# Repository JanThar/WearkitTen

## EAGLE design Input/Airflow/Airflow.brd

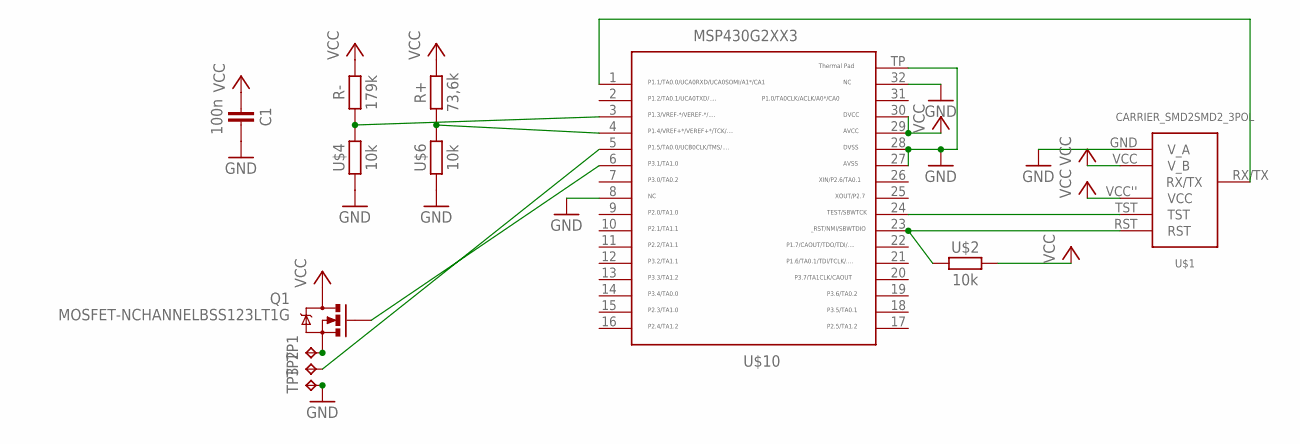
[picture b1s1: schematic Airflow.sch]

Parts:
C1: 100n; 603
Q1: MOSFET-NCHANNELBSS123LT1G; SOT23-3
R+: 73,6k; 603
R-: 179k; 603
TP1, TP2, TP3: TPTP18SQ; TP18SQ
U$1: CARRIER_SMD2SMD2_3POL; CARRIER_SMD2_3POL
U$2, U$4, U$6: 10k; 603
U$10: MSP430G2553; QFN32

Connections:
GND: C1.2, TP3.TP, U$1.GND (V_A), U$4.1, U$6.1, U$10.8, U$10.27, U$10.28, U$10.32, U$10.TP
unnamed: R-.1, U$4.2, U$10.3
unnamed: U$1.TST, U$10.24
unnamed: U$1.RST, U$2.1, U$10.23
unnamed: R+.1, U$6.2, U$10.4
unnamed: TP2.TP, U$10.5
unnamed: Q1.2 (S), TP1.TP
unnamed: Q1.1 (G), U$10.6
unnamed: U$1.RX/TX, U$10.1
VCC: C1.1, Q1.3 (D), R+.2, R-.2, U$1.VCC (V_B), U$1.VCC'' (VCC), U$2.2, U$10.29, U$10.30

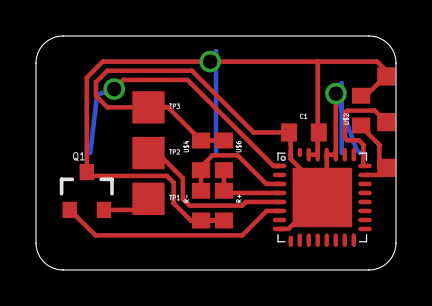
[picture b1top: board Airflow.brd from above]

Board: 2 copper layers, 20.0 x 13.0 mm, 12 parts (0 on the bottom side), 10 nets.

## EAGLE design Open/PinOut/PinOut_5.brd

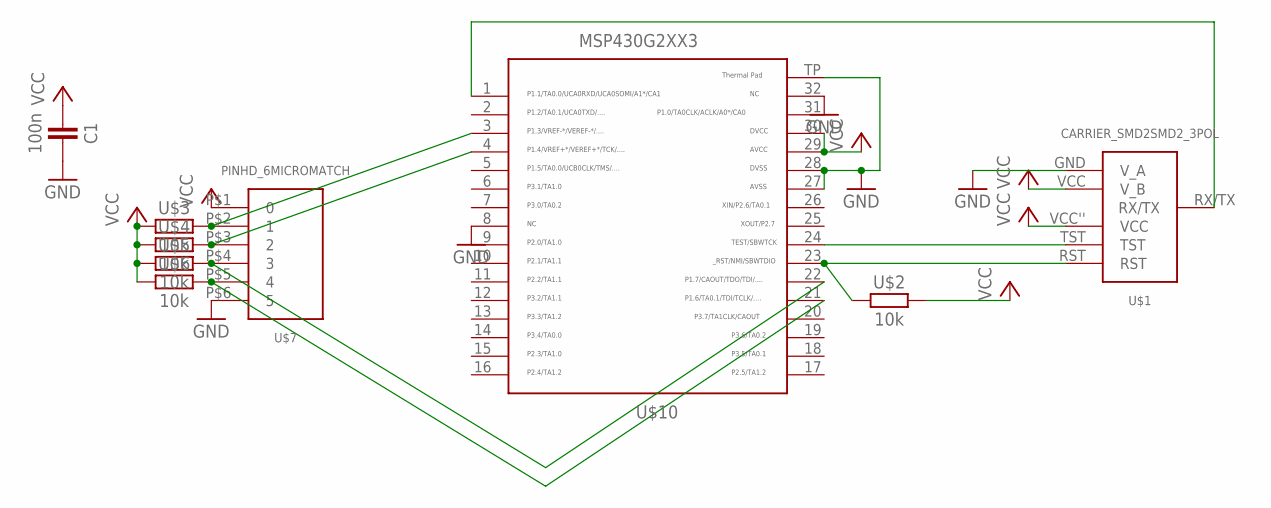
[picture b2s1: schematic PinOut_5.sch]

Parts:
C1: 100n; 603
U$1: CARRIER_SMD2SMD2_3POL; CARRIER_SMD2_3POL
U$2, U$3, U$4, U$5, U$6: 10k; 603
U$7: PINHD_6MICROMATCH; MICROMATCH6POL
U$10: MSP430G2553; QFN32

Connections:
GND: C1.2, U$1.GND (V_A), U$7.P$6 (5), U$10.8, U$10.27, U$10.28, U$10.32, U$10.TP
unnamed: U$5.2, U$7.P$4 (3), U$10.22
unnamed: U$1.TST, U$10.24
unnamed: U$1.RST, U$2.1, U$10.23
unnamed: U$6.2, U$7.P$5 (4), U$10.21
unnamed: U$4.2, U$7.P$3 (2), U$10.4
unnamed: U$3.2, U$7.P$2 (1), U$10.3
unnamed: U$1.RX/TX, U$10.1
VCC: C1.1, U$1.VCC (V_B), U$1.VCC'' (VCC), U$2.2, U$3.1, U$4.1, U$5.1, U$6.1, U$7.P$1 (0), U$10.29, U$10.30

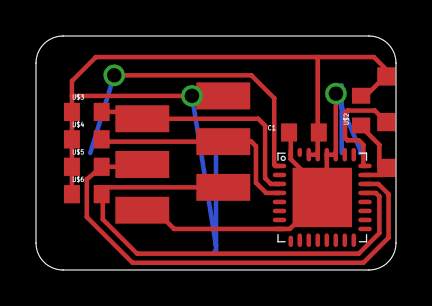
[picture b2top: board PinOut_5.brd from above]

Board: 2 copper layers, 20.0 x 13.0 mm, 9 parts (0 on the bottom side), 9 nets.

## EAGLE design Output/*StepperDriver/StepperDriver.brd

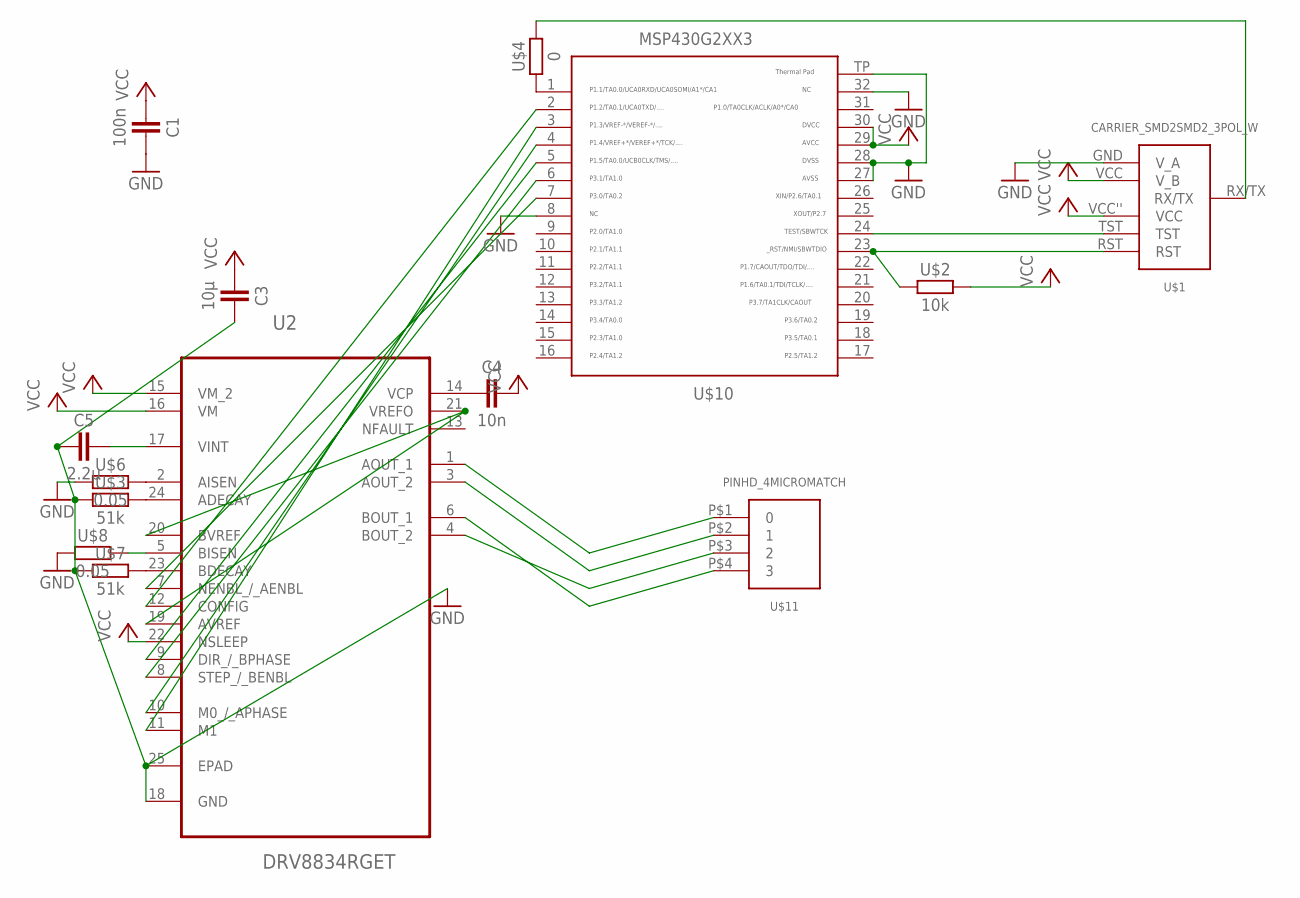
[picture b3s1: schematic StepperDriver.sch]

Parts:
C1: 100n; 603
C3: 10µ; 603
C4: 10n; 603
C5: 2.2µ; 603
U2: DRV8834RGET; QFN50P400X400X100-25N
U$1: CARRIER_SMD2SMD2_3POL_W; CARRIER_SMD2_WIDE_3POL
U$2: 10k; 603
U$3, U$7: 51k; 603
U$4: 0; 603
U$6, U$8: 0.05; 603
U$10: MSP430G2553; QFN32
U$11: PINHD_4MICROMATCH; MICROMATCH4P0L

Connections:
GND: C1.2, C3.2, C5.1, U2.18 (GND), U2.25 (EPAD), U$1.GND (V_A), U$3.1, U$6.1, U$7.1, U$8.1, U$10.8, U$10.27, U$10.28, U$10.32, U$10.TP
unnamed: C5.2, U2.17 (VINT)
unnamed: U$1.TST, U$10.24
unnamed: U$1.RST, U$2.1, U$10.23
unnamed: C4.1, U2.14 (VCP)
unnamed: U2.24 (ADECAY), U$3.2
unnamed: U2.23 (BDECAY), U$7.2
unnamed: U$4.1, U$10.1
unnamed: U$1.RX/TX, U$4.2
unnamed: U2.2 (AISEN), U$6.2
unnamed: U2.5 (BISEN), U$8.2
unnamed: U2.6 (BOUT_1), U$11.P$4 (3)
unnamed: U2.4 (BOUT_2), U$11.P$3 (2)
unnamed: U2.1 (AOUT_1), U$11.P$1 (0)
unnamed: U2.3 (AOUT_2), U$11.P$2 (1)
unnamed: U2.19 (AVREF), U2.20 (BVREF), U2.21 (VREFO)
unnamed: U2.10 (M0_/_APHASE), U$10.4
unnamed: U2.11 (M1), U$10.3
unnamed: U2.7 (NENBL_/_AENBL), U$10.7
unnamed: U2.8 (STEP_/_BENBL), U$10.6
unnamed: U2.12 (CONFIG), U$10.2
unnamed: U2.9 (DIR_/_BPHASE), U$10.5
VCC: C1.1, C3.1, C4.2, U2.15 (VM_2), U2.16 (VM), U2.22 (NSLEEP), U$1.VCC (V_B), U$1.VCC'' (VCC), U$2.2, U$10.29, U$10.30

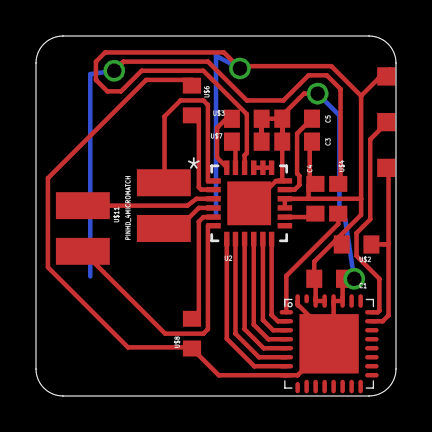
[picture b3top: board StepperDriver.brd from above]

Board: 2 copper layers, 20.0 x 20.0 mm, 14 parts (0 on the bottom side), 23 nets.

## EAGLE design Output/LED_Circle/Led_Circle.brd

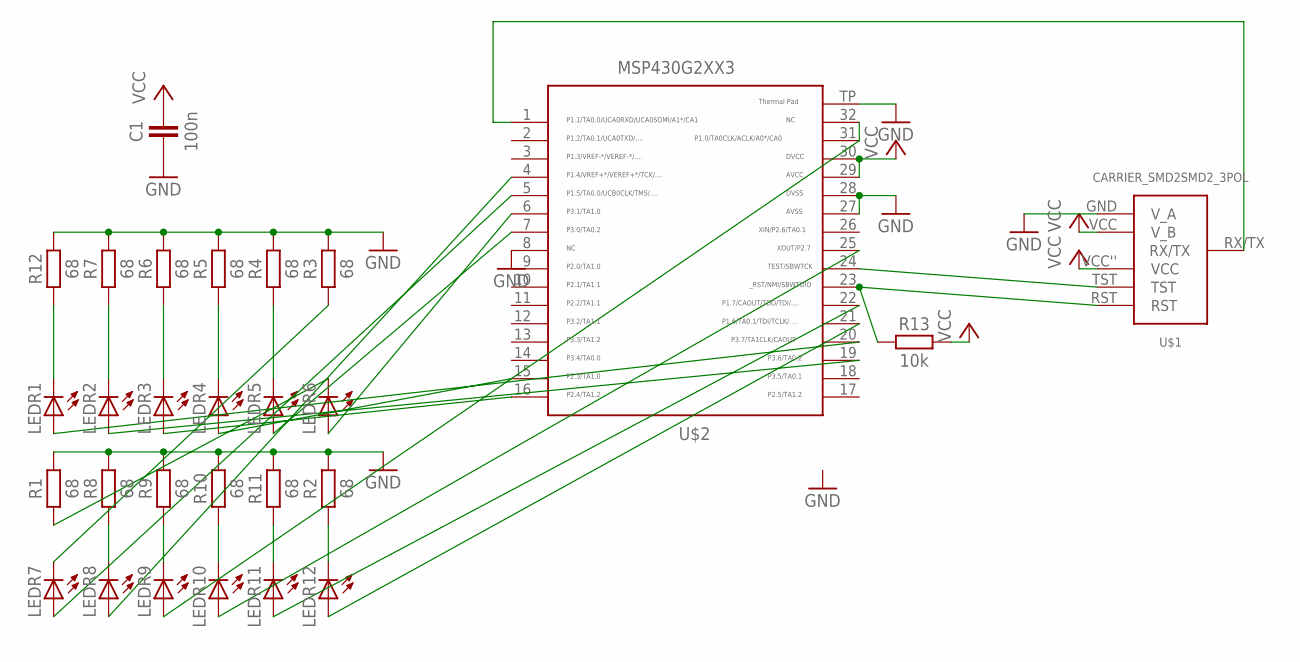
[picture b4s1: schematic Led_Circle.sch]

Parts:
C1: 100n; 603
LEDR1, LEDR2, LEDR3, LEDR4, LEDR5, LEDR6, LEDR7, LEDR8, LEDR9, LEDR10, LEDR11, LEDR12: LEDCHIPLED_0603; CHIPLED_0603
R1, R2, R3, R4, R5, R6, R7, R8, R9, R10, R11, R12: 68; 603
R13: 10k; 603
U$1: CARRIER_SMD2SMD2_3POL; CARRIER_SMD2_3POL
U$2: MSP430G2553; QFN32

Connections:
GND: C1.1, R1.2, R2.2, R3.2, R4.2, R5.2, R6.2, R7.2, R8.2, R9.2, R10.2, R11.2, R12.2, U$1.GND (V_A), U$2.8, U$2.27, U$2.28, U$2.TP
unnamed: LEDR8.A, U$2.4
unnamed: LEDR7.C, R3.1
unnamed: U$1.RX/TX, U$2.1
unnamed: LEDR12.C, R2.1
unnamed: LEDR11.C, R11.1
unnamed: LEDR10.C, R10.1
unnamed: LEDR9.C, R9.1
unnamed: LEDR8.C, R8.1
unnamed: LEDR6.C, R1.1
unnamed: LEDR5.C, R4.1
unnamed: LEDR4.C, R5.1
unnamed: LEDR3.C, R6.1
unnamed: LEDR2.C, R7.1
unnamed: LEDR1.C, R12.1
unnamed: LEDR9.A, U$2.31, U$2.32
unnamed: LEDR10.A, U$2.25
unnamed: LEDR11.A, U$2.22
unnamed: LEDR12.A, U$2.21
unnamed: LEDR1.A, U$2.20
unnamed: LEDR2.A, U$2.19
unnamed: LEDR3.A, U$2.16
unnamed: LEDR4.A, U$2.15
unnamed: LEDR5.A, U$2.7
unnamed: LEDR6.A, U$2.6
unnamed: LEDR7.A, U$2.5
RST: R13.1, U$1.RST, U$2.23
TST: U$1.TST, U$2.24
VCC: C1.2, R13.2, U$1.VCC (V_B), U$1.VCC'' (VCC), U$2.29, U$2.30

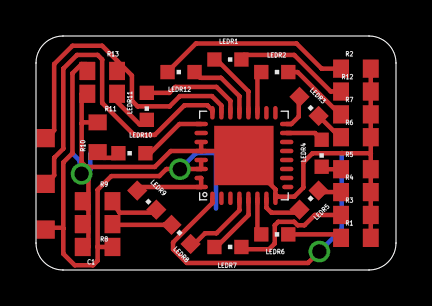
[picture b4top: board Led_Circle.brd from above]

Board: 2 copper layers, 20.0 x 13.0 mm, 28 parts (0 on the bottom side), 29 nets.

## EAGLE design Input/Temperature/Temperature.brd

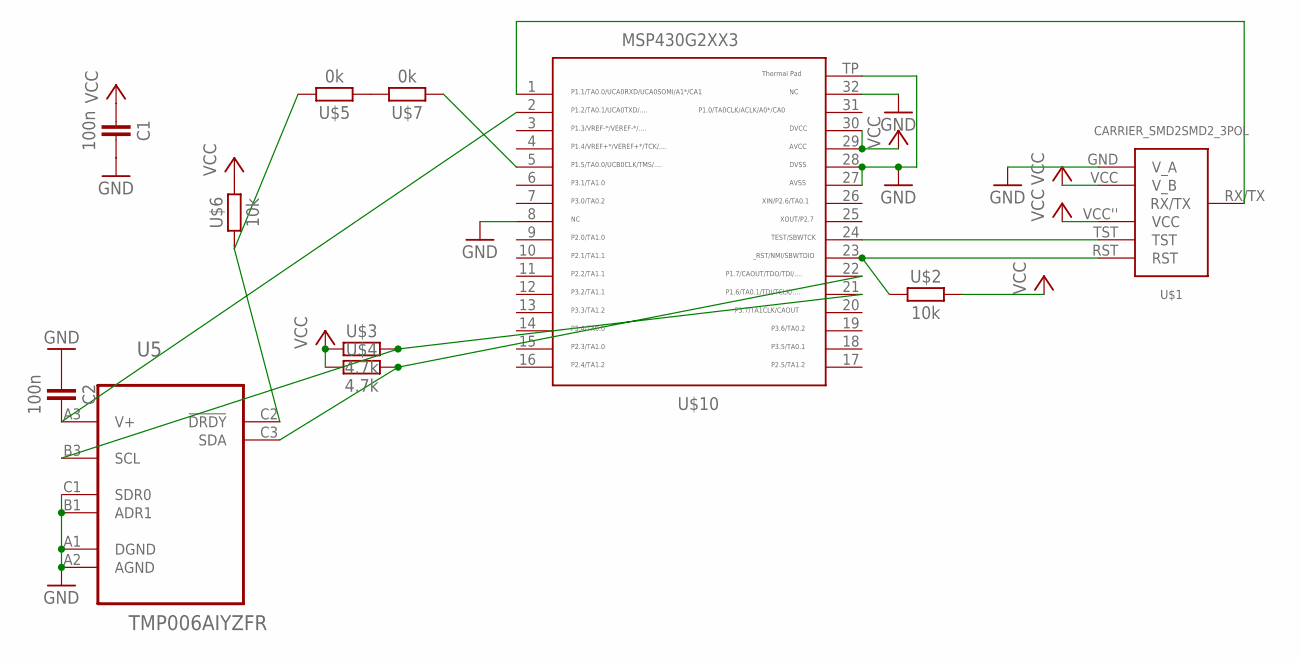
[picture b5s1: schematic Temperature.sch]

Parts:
C1, C2: 100n; 603
U5: TMP006AIYZFR; BGA8C50P3X3_156X156X63
U$1: CARRIER_SMD2SMD2_3POL; CARRIER_SMD2_3POL
U$2, U$6: 10k; 603
U$3, U$4: 4.7k; 603
U$5, U$7: 0k; 603
U$10: MSP430G2553; QFN32

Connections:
GND: C1.2, C2.1, U5.A1 (DGND), U5.A2 (AGND), U5.B1 (ADR1), U5.C1 (SDR0), U$1.GND (V_A), U$10.8, U$10.27, U$10.28, U$10.32, U$10.TP
unnamed: U$7.1, U$10.5
unnamed: U$1.TST, U$10.24
unnamed: U$1.RST, U$2.1, U$10.23
unnamed: U5.C3 (SDA), U$4.2, U$10.22
unnamed: U5.B3 (SCL), U$3.2, U$10.21
unnamed: C2.2, U5.A3 (V+), U$10.2
unnamed: U$5.1, U$7.2
unnamed: U$1.RX/TX, U$10.1
unnamed: U5.C2 (!DRDY), U$5.2, U$6.1
VCC: C1.1, U$1.VCC (V_B), U$1.VCC'' (VCC), U$2.2, U$3.1, U$4.1, U$6.2, U$10.29, U$10.30

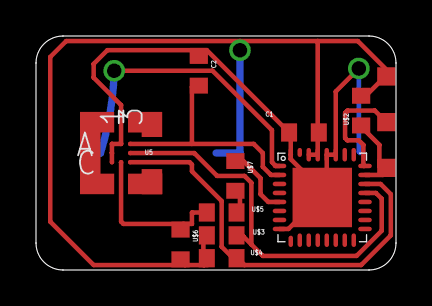
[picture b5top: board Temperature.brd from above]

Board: 2 copper layers, 20.0 x 13.0 mm, 11 parts (0 on the bottom side), 11 nets.

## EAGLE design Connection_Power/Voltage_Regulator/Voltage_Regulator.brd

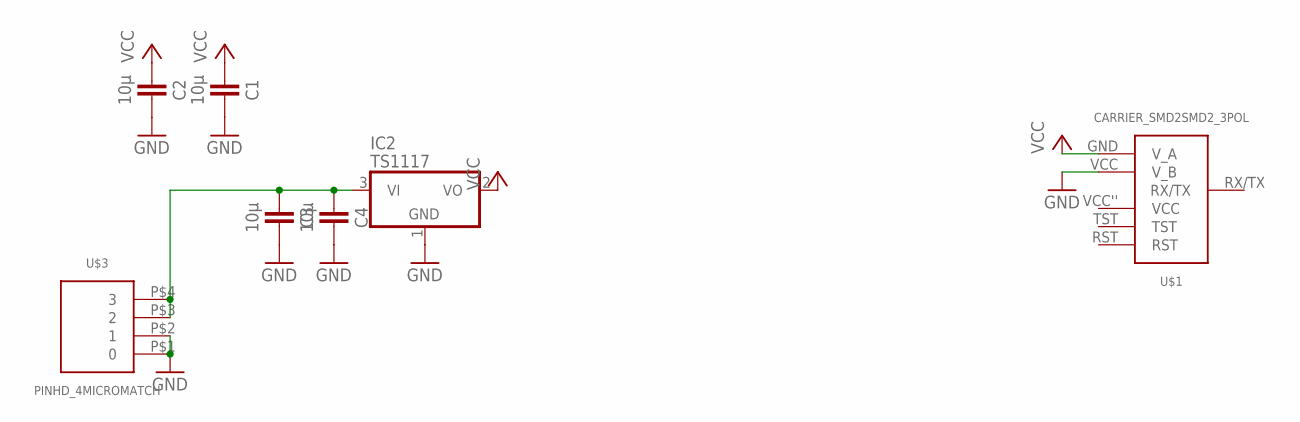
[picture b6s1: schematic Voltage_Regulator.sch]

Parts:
C1, C2, C3, C4: 10µ; 603
IC2: TS1117; SOT223
U$1: CARRIER_SMD2SMD2_3POL; CARRIER_SMD2_3POL
U$3: PINHD_4MICROMATCH; MICROMATCH4P0L

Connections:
GND: C1.2, C2.2, C3.2, C4.2, IC2.1 (GND), U$1.VCC (V_B), U$3.P$1 (0), U$3.P$2 (1)
unnamed: C3.1, C4.1, IC2.3 (VI), U$3.P$3 (2), U$3.P$4 (3)
VCC: C1.1, C2.1, IC2.2 (VO), U$1.GND (V_A)

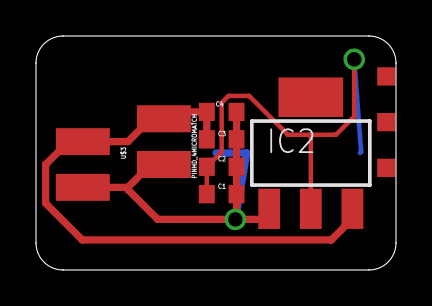
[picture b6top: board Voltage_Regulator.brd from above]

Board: 2 copper layers, 20.0 x 13.0 mm, 7 parts (0 on the bottom side), 3 nets.

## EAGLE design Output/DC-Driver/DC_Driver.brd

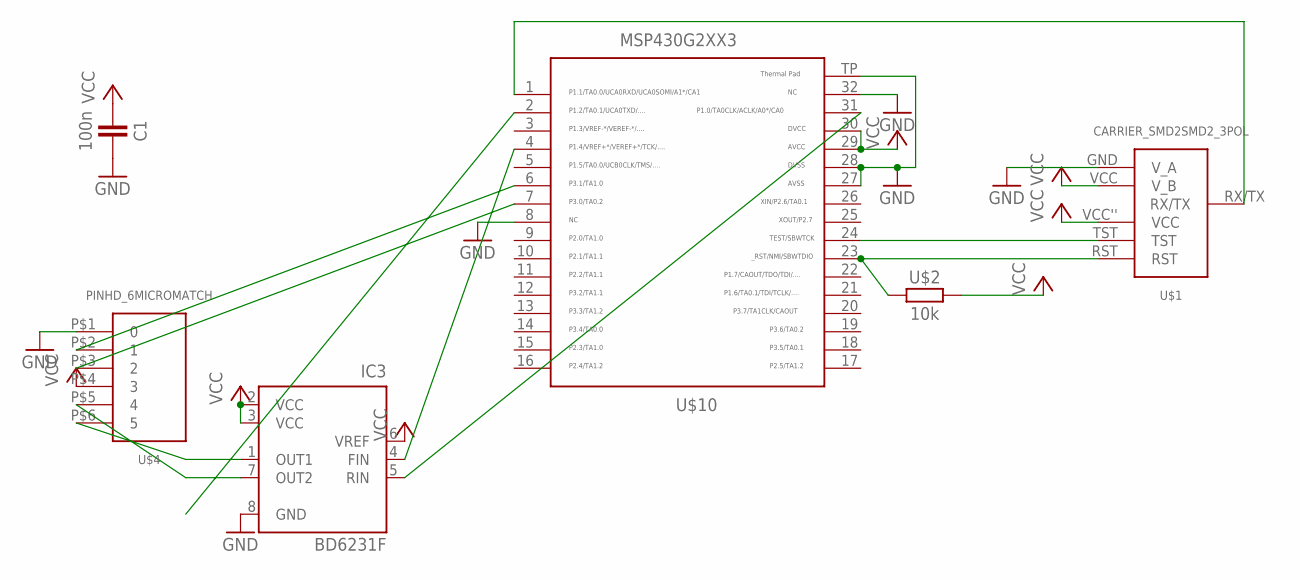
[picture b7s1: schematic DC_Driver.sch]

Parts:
C1: 100n; 603
IC3: BD6231F; SOP8
U$1: CARRIER_SMD2SMD2_3POL; CARRIER_SMD2_3POL
U$2: 10k; 603
U$4: PINHD_6MICROMATCH; MICROMATCH6POL
U$10: MSP430G2553; QFN32

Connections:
GND: C1.2, IC3.8 (GND), U$1.GND (V_A), U$4.P$1 (0), U$10.8, U$10.27, U$10.28, U$10.32, U$10.TP
unnamed: IC3.7 (OUT2), U$4.P$5 (4)
unnamed: U$1.TST, U$10.24
unnamed: U$1.RST, U$2.1, U$10.23
unnamed: IC3.1 (OUT1), U$4.P$6 (5)
unnamed: IC3.4 (FIN), U$10.4
unnamed: IC3.5 (RIN), U$10.31
unnamed: U$1.RX/TX, U$10.1
unnamed: U$4.P$2 (1), U$10.6
unnamed: U$4.P$3 (2), U$10.7
VCC: C1.1, IC3.2 (VCC), IC3.3 (VCC), IC3.6 (VREF), U$1.VCC (V_B), U$1.VCC'' (VCC), U$2.2, U$4.P$4 (3), U$10.29, U$10.30

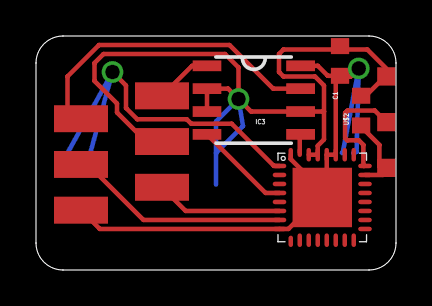
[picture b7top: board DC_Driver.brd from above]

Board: 2 copper layers, 20.0 x 13.0 mm, 6 parts (0 on the bottom side), 11 nets.

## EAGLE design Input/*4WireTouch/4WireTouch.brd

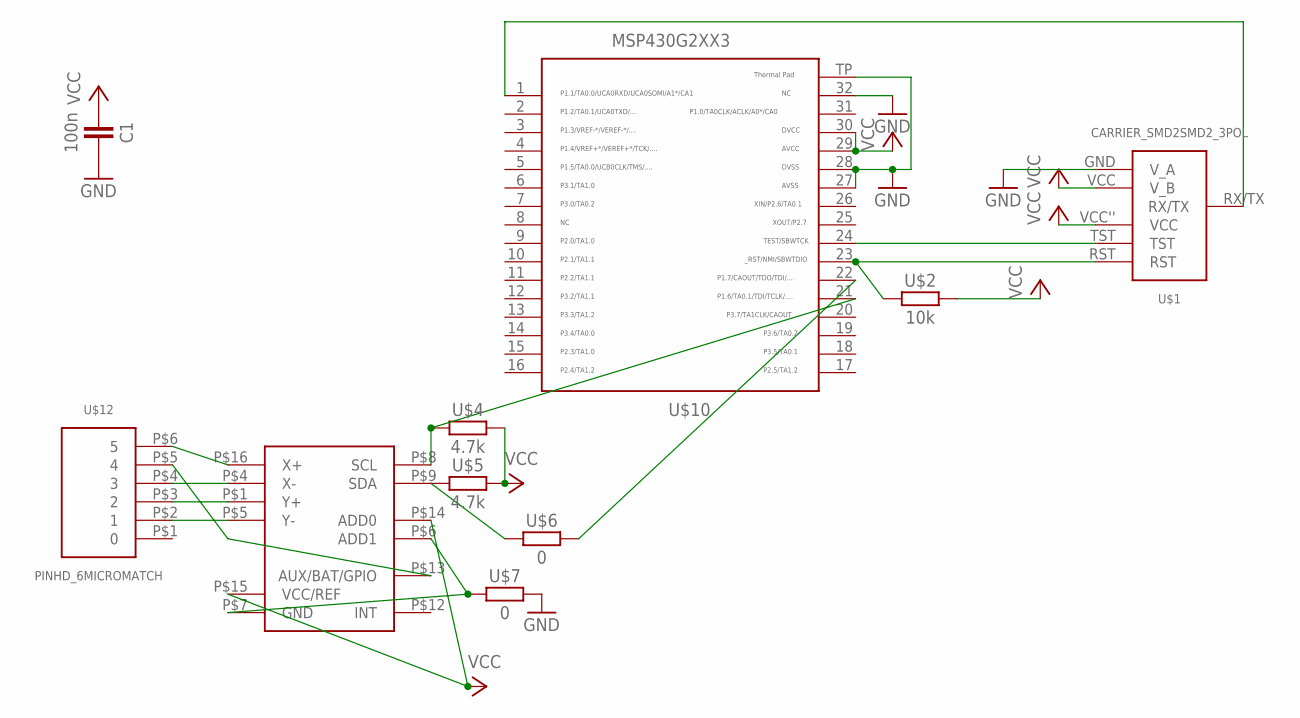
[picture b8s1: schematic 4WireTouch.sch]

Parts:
C1: 100n; 603
U$1: CARRIER_SMD2SMD2_3POL; CARRIER_SMD2_3POL
U$2: 10k; 603
U$3: AD7879; LFCSP
U$4, U$5: 4.7k; 603
U$6, U$7: 0; 603
U$10: MSP430G2553; QFN32
U$12: PINHD_6MICROMATCH; MICROMATCH6POL

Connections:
GND: C1.2, U$1.GND (V_A), U$7.2, U$10.27, U$10.28, U$10.32, U$10.TP
unnamed: U$3.P$8 (SCL), U$4.1, U$10.21
unnamed: U$1.TST, U$10.24
unnamed: U$1.RST, U$2.1, U$10.23
unnamed: U$3.P$9 (SDA), U$5.1, U$6.1
unnamed: U$3.P$13 (AUX/BAT/GPIO), U$12.P$5 (4)
unnamed: U$3.P$5 (Y-), U$12.P$2 (1)
unnamed: U$3.P$4 (X-), U$12.P$4 (3)
unnamed: U$1.RX/TX, U$10.1
unnamed: U$3.P$1 (Y+), U$12.P$3 (2)
unnamed: U$3.P$16 (X+), U$12.P$6 (5)
unnamed: U$6.2, U$10.22
unnamed: U$3.P$6 (ADD1), U$3.P$7 (GND), U$7.1
VCC: C1.1, U$1.VCC (V_B), U$1.VCC'' (VCC), U$2.2, U$3.P$14 (ADD0), U$3.P$15 (VCC/REF), U$4.2, U$5.2, U$10.29, U$10.30

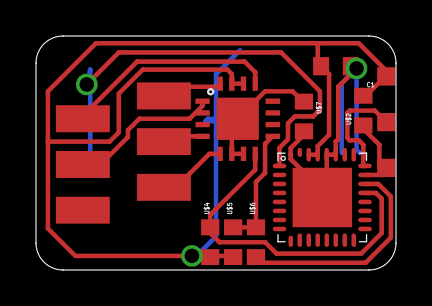
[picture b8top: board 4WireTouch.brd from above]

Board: 2 copper layers, 20.0 x 13.0 mm, 10 parts (0 on the bottom side), 14 nets.

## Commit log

2016-10-31 sort out
2017-02-22 Update Pinheader

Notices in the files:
parts and their libraries:
SparkFun-DiscreteSemi: Licensing: CC v3.0 Share-Alike You are welcome to use this library for commercial purposes.
